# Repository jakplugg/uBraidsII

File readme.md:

# uBraids II; 

### 8hp version of Braids.

#### PCB redesign by J. Matheson. it works with the same firmware, added LED sliders for the 2 oscillator parameters, and drivers to indicate input CVs 

[Google sheets BOM](https://docs.google.com/spreadsheets/d/1qPg4iMz02AhubgOIPSeuag0cT9fuQLDFEAjaWZSTI-4/edit#gid=0)

First there was uBraids, the uModule that started all this Insanity, then Talldog's uBraids SE, with a better display and no AVR programming, now with the same good display and a new easy to use layout, uBraids II!

the main board is easier than the original uBraids, but the display board might be a bit difficult for those new at SMT soldering, 

although the display board is almost the same as talldog's one, it will not fit, there are cutouts for the screws. if you have one you want to use, and modify it for the screws to fit, It will cut a trace that will have to be re-routed with a wire.

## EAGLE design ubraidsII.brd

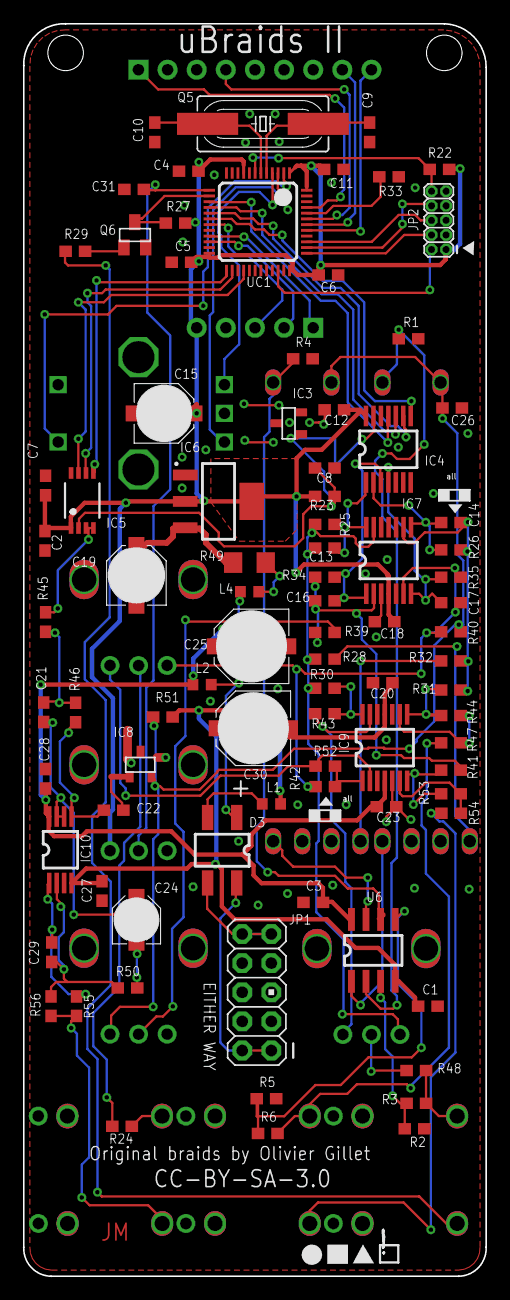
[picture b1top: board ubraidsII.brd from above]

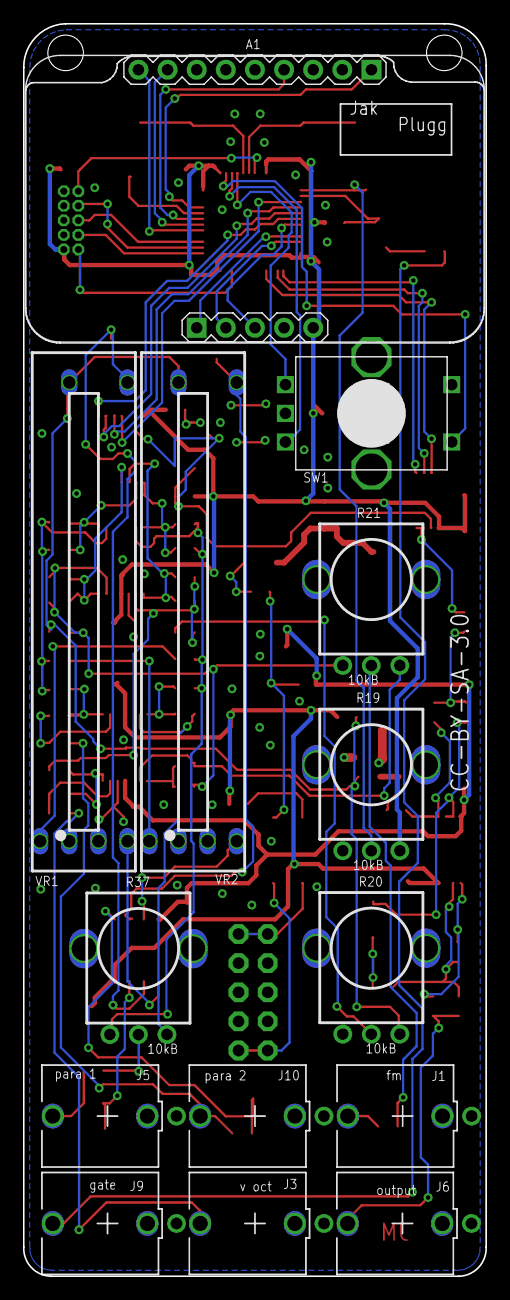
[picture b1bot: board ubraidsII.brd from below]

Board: 2 copper layers, 40.3 x 109.2 mm, 101 parts (14 on the bottom side), 80 nets.

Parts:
A1: DISPLAY-MODULE
C1: 100n; CAP_0603
C2: 100n; CAP_0603_C2
C3: 100n; CAP_0603_C3
C4: 100n; CAP_0603_C4
C5: 100n; CAP_0603_C5
C6: 1u; CAP_0603_C6
C7: 100n; CAP_0603_C7
C8: 470n; CAP_0603_C8
C9: 18p; CAP_0603_C9
C10: 18p; CAP_0603_C10
C11: 100n; CAP_0603_C11
C12: 1u; CAP_0603_C12
C13: 1n; CAP_0603_C13
C14: 1n; CAP_0603_C14
C15: 22u; PANASONIC_C
C16: 1n; CAP_0603_C16
C17: 1n; CAP_0603_C17
C18: 100n; CAP_0603_C18
C19: 22u; PANASONIC_C_C19
C20: 100n; CAP_0603_C20
C21: 100p; CAP_0603_C21
C22: 100p; CAP_0603_C22
C23: 100n; CAP_0603_C23
C24: 10u; PANASONIC_B
C25: 47u; PANASONIC_D
C26: 100n; CAP_0603_C26
C27: 100n; CAP_0603_C27
C28: 100n; CAP_0603_C28
C29: 47p; CAP_0603_C29
C30: 47u; PANASONIC_D_C30
C31: 100n; CAP_0603_C31
D3: SOP-4/6.5x2.54
IC3: LM4040B25; DBZ_R-PDSO-G3
IC4: MCP3204; TSSOP-14
IC5: DAC8551; MSOP-8
IC6: LM1117-3.3; SOT223-4
IC7: MCP6004; TSSOP-14_IC7
IC8: LM4040B10; DBZ_R-PDSO-G3_IC8
IC9: TL074D; TSSOP-14_IC9
IC10: TL072; TSSOP-8
J1: fm; Thonkiconn_Jack
J3: v oct; Thonkiconn_Jack_J3
J5: para 1; Thonkiconn_Jack_J5
J6: output; Thonkiconn_Jack_J6
J9: gate; Thonkiconn_Jack_J9
J10: para 2; Thonkiconn_Jack_J10
JP1: M05X2PTH; AVR_ICSP
JP2: M05X2MINIJTAG; 2X5-1.27
L1: IND_0603
L2: IND_0603_L2
L4: IND_0603_L4
Q5: 8MHz; HC49UP
Q6: MMBT3904; SOT23-BEC
R1: 1.2k; RES_0603
R2: 1.0M; RES_0603_R2
R3: 1.0M; RES_0603_R3
R4: 1.2k; RES_0603_R4
R5: 1.0M; RES_0603_R5
R6: 1.0M; RES_0603_R6
R19: 10kB; 9mm_Alpha/Bourns_Pot
R20: 10kB; 9mm_Alpha/Bourns_Pot_R20
R21: 10kB; 9mm_Alpha/Bourns_Pot_R21
R22: 10k; RES_0603_R22
R23: 1.0k; RES_0603_R23
R24: 100k; RES_0603_R24
R25: 49.9k; RES_0603_R25
R26: 49.9k; RES_0603_R26
R27: 10k; RES_0603_R27
R28: 200k; RES_0603_R28
R29: 100k; RES_0603_R29
R30: 24.9k; RES_0603_R30
R31: 24.9k; RES_0603_R31
R32: 200k; RES_0603_R32
R33: 10k; RES_0603_R33
R34: 24.9k; RES_0603_R34
R35: 24.9k; RES_0603_R35
R37: 10kB; 9mm_Alpha/Bourns_Pot_R37
R39: 120k; RES_0603_R39
R40: 200k; RES_0603_R40
R41: 24.9k; RES_0603_R41
R42: 24.9k; RES_0603_R42
R43: 24.9k; RES_0603_R43
R44: 24.9k; RES_0603_R44
R45: 39k; RES_0603_R45
R46: 39k; RES_0603_R46
R47: 100k; RES_0603_R47
R48: 100k; RES_0603_R48
R49: 4.7; R1206
R50: 24.9k; RES_0603_R50
R51: 330; RES_0603_R51
R52: 24.9k; RES_0603_R52
R53: 24.9k; RES_0603_R53
R54: 100k; RES_0603_R54
R55: 1.0k; RES_0603_R55
R56: 100k; RES_0603_R56
SW1: EC12E_SW; ALPS_EC12E_SW
U6: SOIC-8/150mil
UC1: STM32F103CBT6; LQFP48
VR1: para 1; BOURNS_PTL_30mm
VR2: 10k; BOURNS_PTL_30mm_VR2

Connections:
+3V3: A1.5, C2.1, C4.1, C5.1, C6.1, C7.1, C11.1, C12.1, C15.+, C18.1, IC4.14, IC5.1, IC6.2, IC6.4, IC7.4, JP2.1, R19.3, R22.2, R23.1, R27.2, UC1.1, UC1.9, UC1.24, UC1.36, UC1.48
ADC_MISO: IC4.10, UC1.16
ADC_MOSI: IC4.9, UC1.17
ADC_SCK: IC4.11, UC1.15
ADC_SS: IC4.8, UC1.18
AREF: C8.1, IC3.1, IC4.13, IC5.2, R23.2
AREF_-10: C26.1, IC8.2, R20.3, R40.1, R51.2, VR1.3, VR2.3
AUDIO_OUT: IC5.3, IC5.4, R45.2
BOOT_FLASH: R33.2, UC1.44
DAC_MOSI: IC5.7, UC1.28
DAC_SCK: IC5.6, UC1.26
DAC_SS: IC5.5, UC1.25
DISP_CHAR0: A1.9, UC1.43
DISP_CHAR1: A1.6, UC1.45
DISP_CHAR2: A1.14, UC1.41
DISP_CHAR3: A1.13, UC1.42
DISP_EN: A1.1, UC1.21
DISP_SCK: A1.2, UC1.22
DISP_SER: A1.3, UC1.19
ENC_A: SW1.B, UC1.3
ENC_B: SW1.A, UC1.4
ENC_CLICK: SW1.E, UC1.2
FINE_TUNE: C31.1, R19.2, UC1.13
FM_CV: C17.2, IC4.4, IC7.7, R35.2
GATE: Q6.C, R27.1, UC1.14
GND: A1.4, A1.7, A1.8, A1.10, A1.11, A1.12, C1.2, C2.2, C3.1, C4.2, C5.2, C6.2, C7.2, C8.2, C9.1, C10.1, C11.2, C12.2, C15.-, C18.2, C19.-, C20.1, C22.2, C23.2, C25.-, C26.2, C27.1, C28.2, C30.+, C31.2, IC3.2, IC4.7, IC4.12, IC5.8, IC6.1, IC7.3, IC7.5, IC7.10, IC7.11, IC7.12, IC8.1, IC9.3, IC9.5, IC9.10, IC9.12, IC10.3, J1.3, J3.3, J5.3, J6.3, J9.3, J10.3, JP1.3, JP1.4, JP1.5, JP1.6, JP1.7, JP1.8, JP2.3, JP2.5, JP2.9, Q6.E, R1.2, R2.1, R4.2, R5.1, R19.1, R19.4, R19.5, R20.1, R20.4, R20.5, R21.4, R21.5, R33.1, R37.4, R37.5, SW1.C, SW1.D, SW1.GND1, SW1.GND2, UC1.8, UC1.20, UC1.23, UC1.35, UC1.46, UC1.47, VR1.1, VR2.1
JTCK: JP2.4, UC1.37
JTDI: JP2.8, UC1.38
JTDO: JP2.6, UC1.39
JTMS: JP2.2, UC1.34
unnamed: R2.2, R3.2, U6.3
unnamed: C9.2, Q5.2, UC1.5
unnamed: C10.2, Q5.1, UC1.6
unnamed: IC9.7, R41.1, R53.2
unnamed: R20.2, R39.1
unnamed: R1.1, U6.2, VR1.5
unnamed: C16.1, IC7.2, R34.1, R39.2, R41.2
unnamed: IC9.6, R53.1, R54.2
unnamed: R21.2, R24.2
unnamed: C19.+, IC6.3, R49.1
unnamed: IC9.13, R37.3, R43.1
unnamed: IC9.14, R30.1, R43.2
unnamed: IC9.2, R21.3, R52.1
unnamed: IC9.1, R42.1, R52.2
unnamed: C17.1, IC7.6, R21.1, R35.1, R40.2, R42.2
unnamed: D3.4, JP1.1, JP1.2
unnamed: IC9.8, R31.1, R44.2
unnamed: C13.1, IC7.13, R25.1, R28.2, R30.2, R37.1
unnamed: R28.1, VR1.2
unnamed: R37.2, R48.2
unnamed: IC9.9, R44.1, R47.2
unnamed: D3.3, JP1.9, JP1.10
unnamed: R32.1, VR2.2
unnamed: Q6.B, R29.2
unnamed: C21.2, C24.+, IC10.6, IC10.7
unnamed: C24.-, R50.2
unnamed: C22.1, IC10.5, R46.1
unnamed: C14.1, IC7.9, R26.1, R31.2, R32.2
unnamed: C21.1, R45.1, R46.2
unnamed: J6.2, R55.1, R56.1
unnamed: C29.2, IC10.1, R55.2
unnamed: C29.1, IC10.2, R50.1, R56.2
Net_0: J9.2, R29.1
Net_1: J3.2, R54.1
Net_2: J5.2, R3.1, R48.1
Net_3: U6.7, VR2.6
Net_12: U6.1, VR1.6
Net_42: J1.2, R24.1
Net_55: J10.2, R6.1, R47.1
Net_80: R4.1, U6.6, VR2.5
Net_81: R5.2, R6.2, U6.5
Net_106: D3.1, L2.2, L4.1
Net_107: D3.2, L1.2
Net_110: L4.2, R49.2
PARAM1_CV: C13.2, IC4.1, IC7.14, R25.2
PARAM2_CV: C14.2, IC4.2, IC7.8, R26.2
PITCH_CV: C16.2, IC4.3, IC7.1, R34.2
RESET: JP2.10, R22.1, UC1.7
VCC: C3.2, C23.1, C25.+, C28.1, IC9.4, IC10.8, L2.1, U6.8
VEE: C1.1, C20.2, C27.2, C30.-, IC9.11, IC10.4, L1.1, R51.1, U6.4

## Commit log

2018-08-03 :space_invader: Added .gitattributes & .gitignore files
2018-08-03 initial upload
    initial patreon upload
2018-08-17 added ubraidsII panel
    panel files added
2018-08-17 small change to panel dip file
    removed text from unused assembly layer
2018-09-02 unlocked files
    thanks, patreons!
2018-09-02 update disp gerb
    removed feducials from display board
2018-09-02 updated text
    changed some words
2018-10-18 experimental eagle export
    exported eagle files from diptrace beta.
2018-11-27 removed CNC panel
2019-01-23 Panel FPD
2020-01-23 schematic pdf
2023-02-20 Update readme.md
    spelling

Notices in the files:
ubraidsII.brd:
CC-BY-SA-3.0
